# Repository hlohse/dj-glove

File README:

Windows
------------

Make sure the following software is installed:

    Visual Studio Express 2013
    Arduino IDE

To make use of virtual MIDI ports, use the following 3rd party software:

    Go to http://www.tobias-erichsen.de/
    Download and install loopMIDI
    Download the virtualMIDI SDK
    Copy the following virtualMIDI SDK C files to the ThirdParty directory:
        teVirtualMidi.h
        teVirtualMidi32.lib

Linux (Ubuntu 14.04)
-------------------------

Make sure the following packages are installed:

    g++ (>= 4.8)
    arduino
    libasound2-dev
    libbluetooth-dev

All Platforms
------------------

Pair your PC with the Arduino's Bluetooth module using the PIN 1234.

Adjust default Bluetooth address to your module's in PC/BluetoothDevice.cpp, BluetoothDevice::Arduino.

=========
  Misc
=========

Advanced project of Robotics Lab ST14, University of Heidelberg, Germany.
Authors: Jan-Lukas Tirpitz, Henning Lohse
Supervisors: Karsten Krispin, Thomas Kloepfer

Demo:
https://www.youtube.com/watch?v=biKKQlQEOuE

Project website (German): 
http://ornella.iwr.uni-heidelberg.de/ROBOTICSLAB/ROBPROJECTS/COMPLETED/2014SS_DJHANDSCHUH/index.html

Robotics Lab website:
http://joanna.iwr.uni-heidelberg.de/rlab/en/about

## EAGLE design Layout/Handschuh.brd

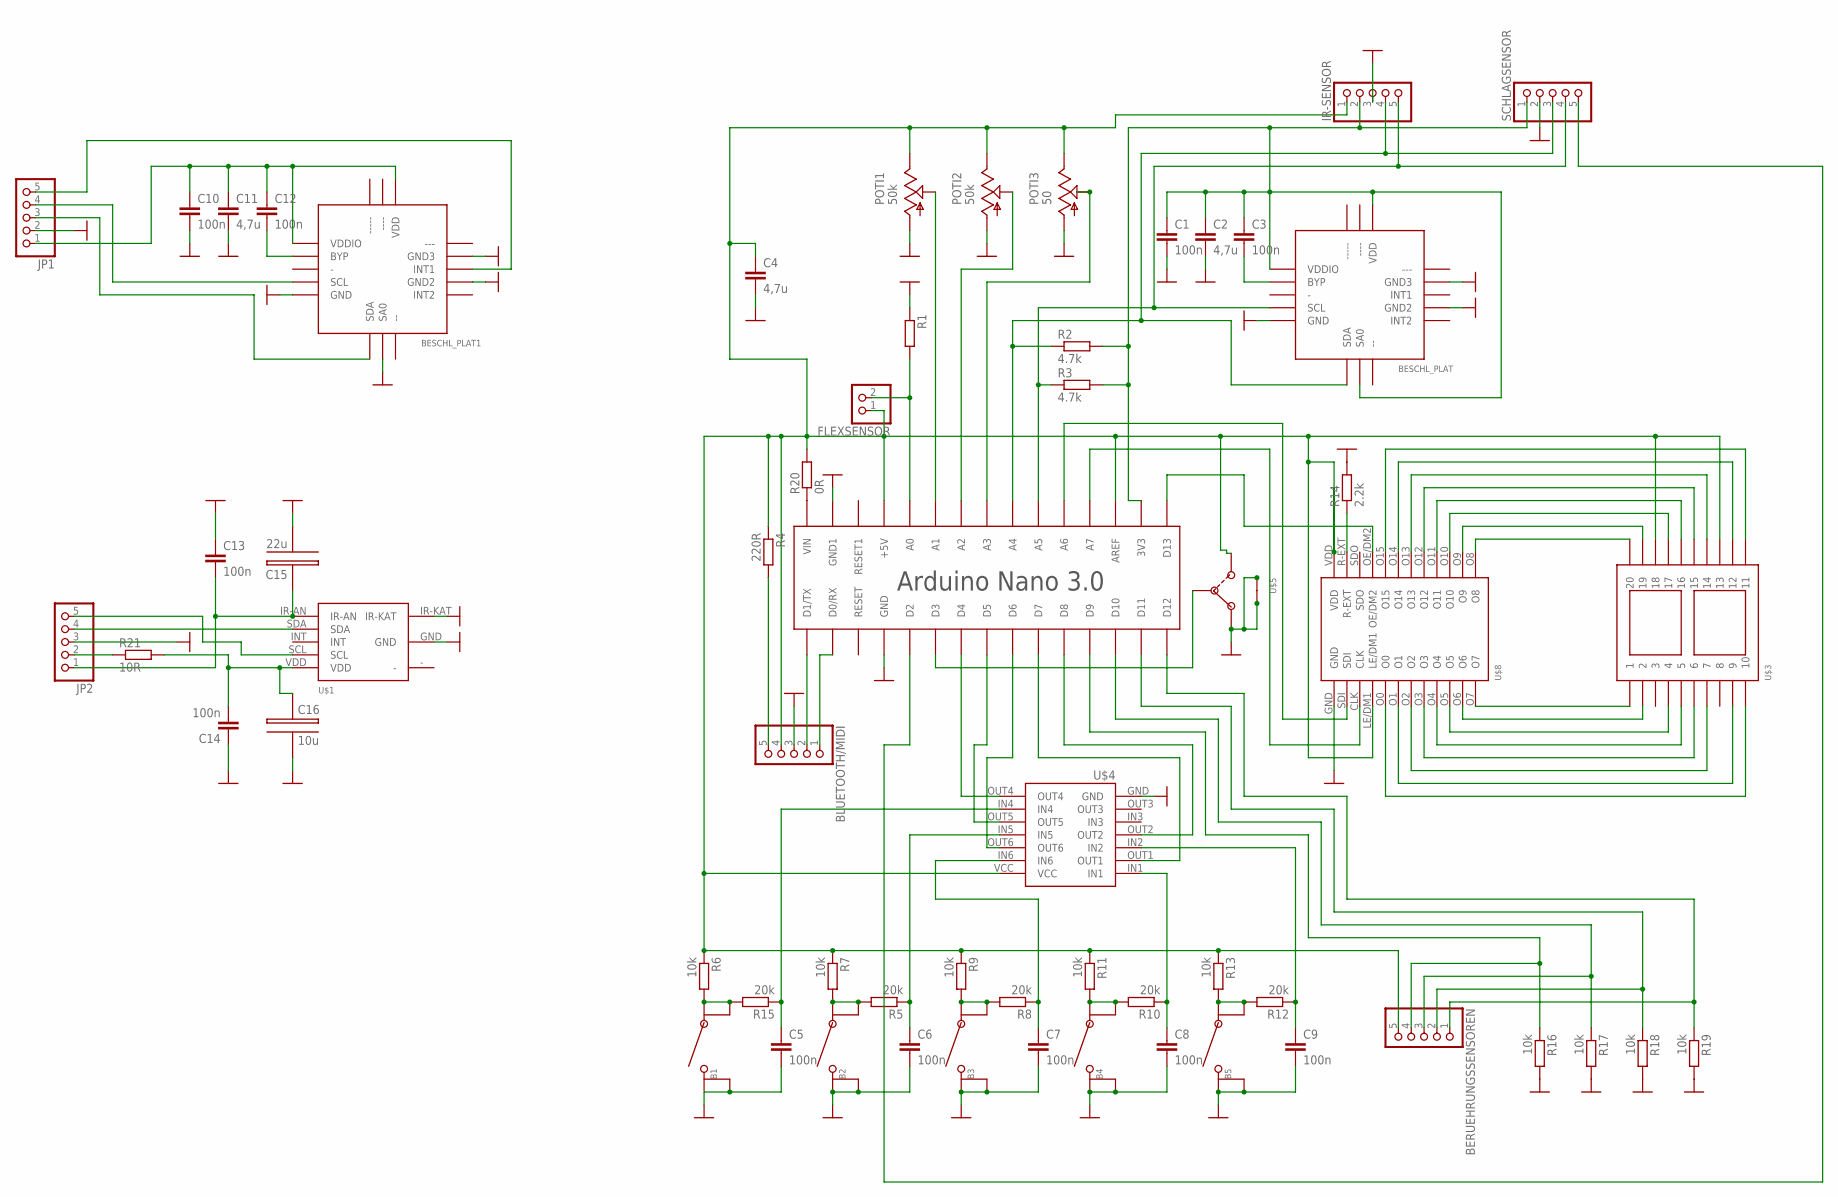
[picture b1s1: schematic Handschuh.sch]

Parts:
B1, B2, B3, B4, B5: BUTTON
BERUEHRUNGSSENSOREN: PINHD-1X5/90; 1X05/90
BESCHL_PLAT, BESCHL_PLAT1: BESCHLEUNIGSUNGSSENSOR; BESCHLEUNIGUNGSSENSOR
BLUETOOTH/MIDI: PINHD-1X5/90; 1X05/90
C1, C3, C5, C6, C7, C8, C9, C10, C12, C13, C14: 100n; C0805
C2, C4, C11: 4,7u; C0805
C15: 22u; 22U-KONDENSATOR
C16: 10u; 22U-KONDENSATOR
FLEXSENSOR: PINHD-1X2/90; 1X02/90
IR-SENSOR: PINHD-1X5/90; 1X05/90
JP1, JP2: PINHD-1X5/90; 1X05/90
POTI1, POTI2: 50k; POTI
POTI3: 50; POTI
R1: R-EU_M0805; M0805
R2, R3: 4.7k; M0805
R4: 220R; M0805
R5, R8, R10, R12, R15: 20k; M0805
R6, R7, R9, R11, R13, R16, R17, R18, R19: 10k; M0805
R14: 2.2k; M0805
R20: 0R; M0805
R21: 10R; M0805
SCHLAGSENSOR: PINHD-1X5/90; 1X05/90
U$1: IR-SENSOR
U$2: ARDUINONANO; PDIP-32
U$3: 7-SEGMENT
U$4: SCHMITT-TRIGGER
U$5: SCHALTER
U$8: 7-SEGMENT-TREIBER

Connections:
3,3V: BESCHL_PLAT.SA0, BESCHL_PLAT.VDD, BESCHL_PLAT.VDDIO, C1.1, C2.1, C3.1, IR-SENSOR.2, R2.2, R3.2, SCHLAGSENSOR.1, U$2.3V3
3,3V1: BESCHL_PLAT1.VDD, BESCHL_PLAT1.VDDIO, C10.1, C11.1, C12.1, JP1.1
5V: BERUEHRUNGSSENSOREN.5, BLUETOOTH/MIDI.4, C4.1, FLEXSENSOR.1, IR-SENSOR.1, POTI1.VCC, POTI2.VCC, POTI3.VCC, R4.1, R6.1, R7.1, R9.1, R11.1, R13.1, R20.2, U$2.+5V, U$2.AREF, U$3.13, U$3.18, U$4.VCC, U$5.3, U$8.LE/DM1, U$8.VDD
GND: B1.2, B2.2, B3.2, B4.2, B5.2, BESCHL_PLAT.GND, BESCHL_PLAT.GND2, BESCHL_PLAT.GND3, BESCHL_PLAT1.GND, BESCHL_PLAT1.GND2, BESCHL_PLAT1.GND3, BESCHL_PLAT1.SA0, BLUETOOTH/MIDI.3, C1.2, C2.2, C4.2, C5.2, C6.2, C7.2, C8.2, C9.2, C10.2, C11.2, C13.1, C14.1, C15.-, C16.-, IR-SENSOR.3, JP1.2, JP2.3, POTI1.GND, POTI2.GND, POTI3.GND, R1.1, R14.2, R16.2, R17.2, R18.2, R19.2, SCHLAGSENSOR.2, U$1.GND, U$1.IR-KAT, U$2.GND, U$2.GND1, U$4.GND, U$5.1, U$5.4, U$5.5, U$8.GND
unnamed: R20.1, U$2.VIN
unnamed: BESCHL_PLAT1.BYP, C12.2
unnamed: B1.3, B1.4, R6.2, R15.2
unnamed: FLEXSENSOR.2, R1.2, U$2.A0
unnamed: BESCHL_PLAT.BYP, C3.2
unnamed: SCHLAGSENSOR.5, U$2.D2
unnamed: POTI1.VALUE, U$2.A1
unnamed: POTI2.VALUE, U$2.A2
unnamed: POTI3.VALUE, U$2.A3
unnamed: BESCHL_PLAT1.SCL, JP1.4
unnamed: BLUETOOTH/MIDI.2, U$2.D1/TX
unnamed: BLUETOOTH/MIDI.1, U$2.D0/RX
unnamed: BLUETOOTH/MIDI.5, R4.2
unnamed: BESCHL_PLAT1.SDA, JP1.3
unnamed: C6.1, R5.1, U$4.IN5
unnamed: B2.3, B2.4, R5.2, R7.2
unnamed: C7.1, R8.1, U$4.IN6
unnamed: B3.3, B3.4, R8.2, R9.2
unnamed: C8.1, R10.1, U$4.IN1
unnamed: B4.3, B4.4, R10.2, R11.2
unnamed: C9.1, R12.1, U$4.IN2
unnamed: B5.3, B5.4, R12.2, R13.2
unnamed: U$2.D4, U$4.OUT4
unnamed: U$2.D5, U$4.OUT5
unnamed: U$2.D6, U$4.OUT6
unnamed: U$2.D7, U$4.OUT1
unnamed: U$2.D8, U$4.OUT2
unnamed: U$2.A6, U$8.SDI
unnamed: C5.1, R15.1, U$4.IN4
unnamed: U$2.A7, U$8.CLK
unnamed: U$3.9, U$8.O1
unnamed: U$3.1, U$8.O7
unnamed: U$3.2, U$8.O6
unnamed: U$3.4, U$8.O5
unnamed: U$3.5, U$8.O4
unnamed: U$3.6, U$8.O3
unnamed: U$3.7, U$8.O2
unnamed: U$3.10, U$8.O0
unnamed: U$3.20, U$8.O8
unnamed: U$3.19, U$8.O9
unnamed: U$3.17, U$8.O10
unnamed: U$3.16, U$8.O11
unnamed: U$3.15, U$8.O12
unnamed: U$3.14, U$8.O13
unnamed: U$3.12, U$8.O14
unnamed: U$3.11, U$8.O15
unnamed: BERUEHRUNGSSENSOREN.4, R16.1, U$2.D9
unnamed: R14.1, U$8.R-EXT
unnamed: U$2.D13, U$8.OE/DM2
unnamed: BESCHL_PLAT1.INT1, JP1.5
unnamed: BERUEHRUNGSSENSOREN.3, R17.1, U$2.D10
unnamed: BERUEHRUNGSSENSOREN.2, R18.1, U$2.D11
unnamed: BERUEHRUNGSSENSOREN.1, R19.1, U$2.D12
unnamed: U$2.D3, U$5.2
unnamed: BESCHL_PLAT.SCL, IR-SENSOR.5, R3.1, SCHLAGSENSOR.4, U$2.A5
unnamed: C13.2, C15.+, JP2.1, U$1.IR-AN
unnamed: C14.2, C16.+, R21.2, U$1.VDD
unnamed: BESCHL_PLAT.SDA, IR-SENSOR.4, R2.1, SCHLAGSENSOR.3, U$2.A4
unnamed: JP2.2, R21.1
unnamed: JP2.4, U$1.SDA
unnamed: JP2.5, U$1.SCL

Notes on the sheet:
Arduino Nano 3.0

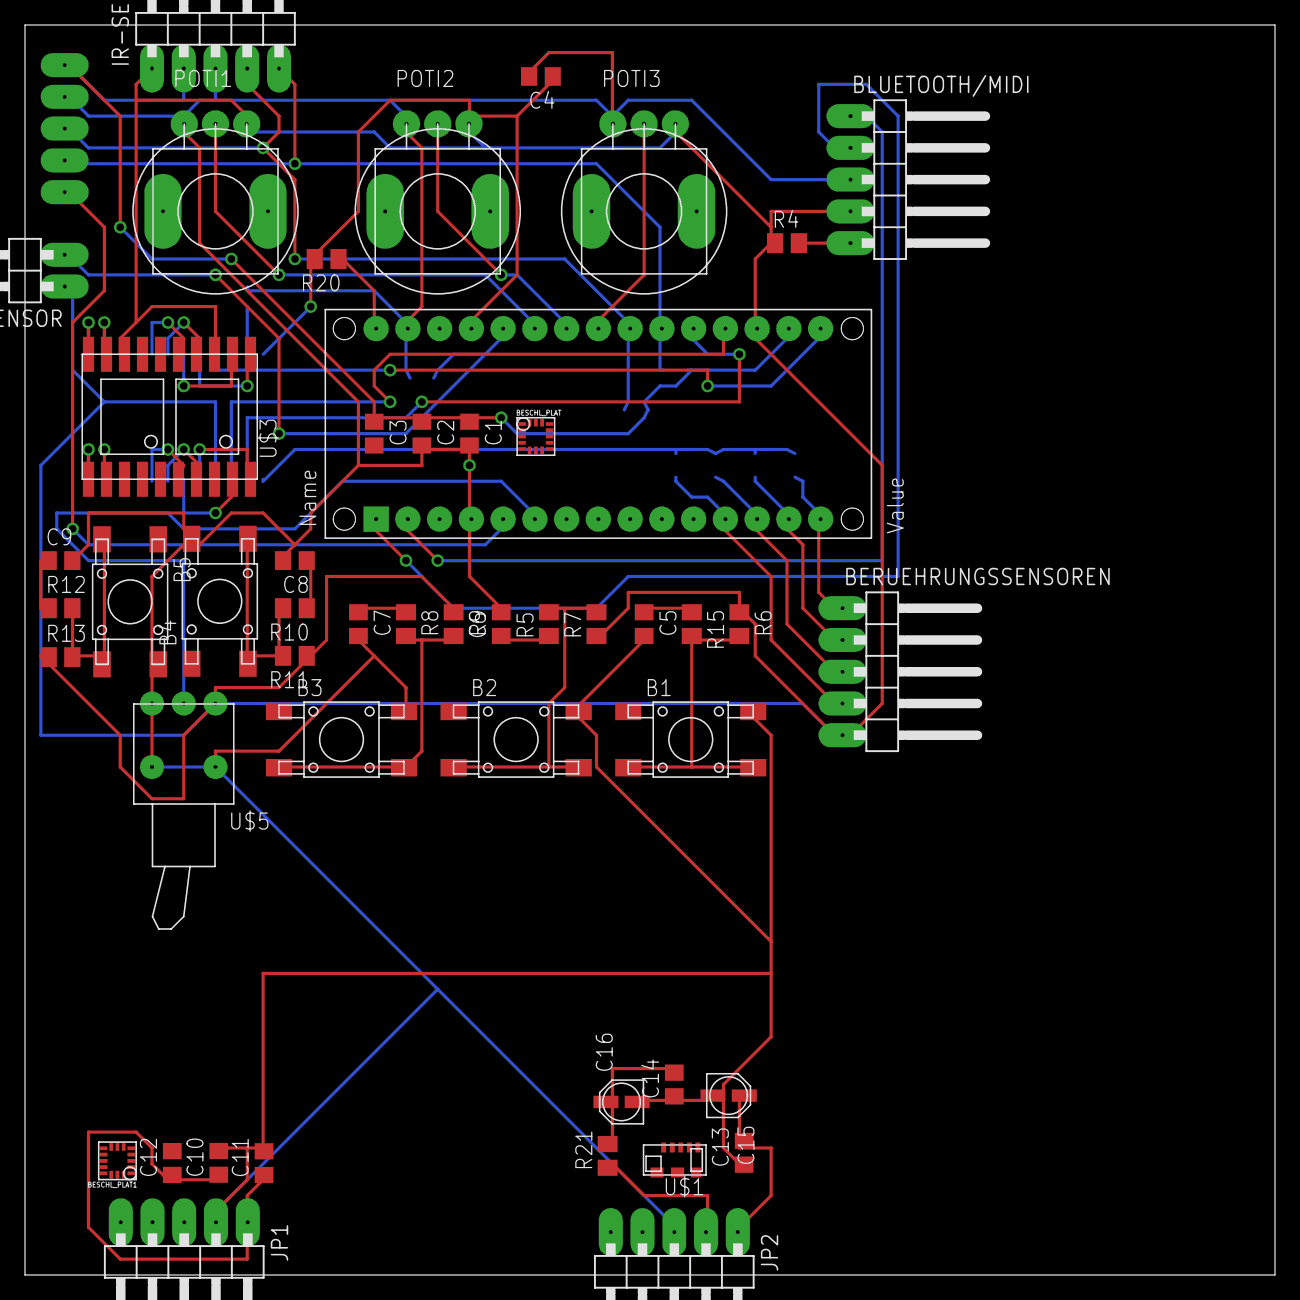
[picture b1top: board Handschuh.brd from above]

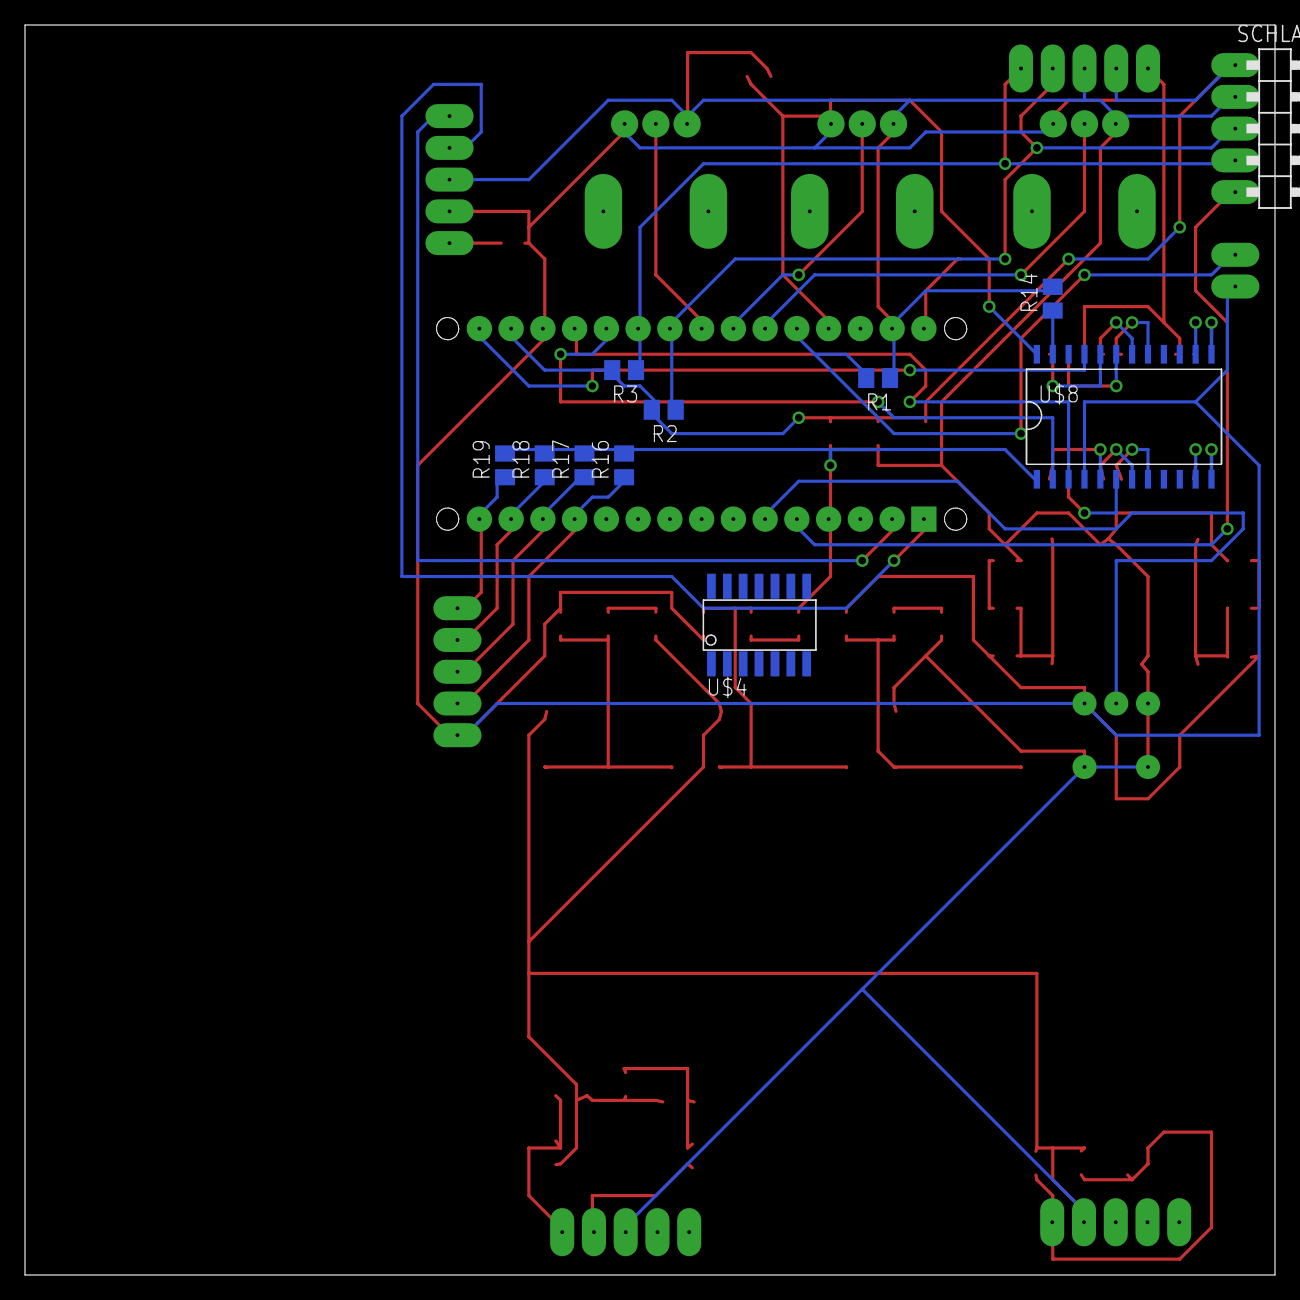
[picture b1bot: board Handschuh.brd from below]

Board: 2 copper layers, 100.0 x 100.0 mm, 60 parts (11 on the bottom side), 65 nets.

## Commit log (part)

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2014-06-17 * Added .gitignore * Ignores C++ and VisualStudio files (via GitHub)
2014-06-17 * Added build, lib, inc and src directories * build, inc and src have arduino and midiserver subdirs
2014-06-17 Revert "Added Arduino Blink basic example to sources"
    This reverts commit 96d4ca2e5d37cda4671e8fc9c7b83ebec26619f9.
2014-06-17 Revert "* Added build, lib, inc and src directories"
    This reverts commit 876984708795c58a9c3cb623dbc15fad2306fee0.
2014-06-18 Added upload.sh Bash script for easy binary upload
2014-06-19 Revert "Started Makefile including Arduino processing,"
    This reverts commit 1aae7c41ad6667d9326a8a3ee617025c9303064b.
2014-06-19 Revert "Added upload.sh Bash script for easy binary upload"
    This reverts commit 5ea77c0251e6820b0246ce1e51268587c1eec1c7.
2014-06-19 PC directory now has just common subdirectory. Projects will need their own directory
2014-06-19 Added Arduino.mk from https://github.com/sudar/Arduino-Makefile
2014-06-19 Added Bluetooth to Arduino common libs. It provides a SoftwareSerial and setup function for Bluetooth communication
2014-06-21 Compilable BtPingPong stub with Makefile
2014-06-21 * Added top-level Makefile * Executes Makefile for each project in Arduino directory * Can be configured via Config.mk
2014-06-21 Ignore .swo
2014-06-21 Implemented Arduino BtPingPong
2014-06-21 Implemented ISerial interface
2014-06-21 Added WaitUntilAvailable and GetLastError to ISerial
2014-06-21 * Renamed ISerial to Serial * Serial implements several methods using abstract methods * Removed code stubs from Bluetooth implemented by Serial
2014-06-21 Ignore *.run
2014-06-21 * Changed Serial to ISerial interface * Added ISerial::ReadNextAvailable * Changed Serial implementation to CommonSerial
2014-06-22 BluetoothDevice uses channel, constructs socket address correctly
2014-06-22 CommonSerial implements ISerial::GetLastError
2014-06-22 Implemented Bluetooth::Connect to connect to given device via Bluetooth RFCOMM socket
2014-06-22 Refactorings Bluetooth
2014-06-22 * Moved Platform.h to root directory * Added Bluetooth Channel and MAC
2014-06-22 ISerial's declared functions must take length parameter
2014-06-22 Fixed false implicit type casting of BluetoothDevice::channel_
2014-06-22 * Adopted ISerial changes to Bluetooth * As ioctl returns size of next message and not all socket data, WaitUntilAvailable uses read to buffer into buffer_ internally until the requested length is bu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
2014-06-22 * Fixed missing ISerial virtual destructor * Directory common in root directory to share infos between Arduino and PC projects * Move Platform.h to common * Created BtLatency.h in common to configure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
2014-06-26 Fixed make clean
2014-06-26 Added BluetoothCommands providing AT commands to configure Bluetooth module
2014-07-01 Heavily changed project structure: * Arduino projects are no longer compiled via Makefile * Use IDE to compile Arduino project from their ino file * Copy/link libraries into Arduino installation fold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
2014-07-01 Added Visual Studio 2013 solution
2014-07-01 Ported Bluetooth to Windows
2014-07-03 * Added Bluetooth::SetUp/::TearDown for Winsock init/cleanup * Link against Winsock2 library
2014-07-03 * BluetoothDevice uses channel as port on Windows * Bluetooth uses send/recv instead of _write/_read for Windows sockets
2014-07-03 * BtLatency project correctly links againt libdj-glove.dll/.lib * Needs keypress to terminate
2014-07-03 Implemented MidiSignal
2014-07-03 Implemented MidiPort for Windows using teVirtualMIDI
2014-07-05 * Midi declared byte/word types * enum instead of enum class as avr-gcc lacks the latter somehow * SplitPitchBend function
2014-07-05 Midi::CombinePitchBend
2014-07-05 * Moved bit fiddle code from MidiChannel to Midi * Comments for MidiChannel
2014-07-05 Added Missing class scope
2014-07-05 Implemented Entchen Arduino project. After receiving start signal '!', it sends MIDI signals playing Alle meine Entchen via Bluetooth :)
2014-07-05 * MidiChannel channel can be set later/changed * SignalLength returns number of Signal bytes
2014-07-05 Implemented MidiPlayer Arduino library. Provides a set of channels that can be played via Bluetooth. Sends number of signal bytes before 2-3 MIDI signal bytes
2014-07-05 MidiPlayer comments
2014-07-10 BtConfig Arduino project to change Bluetooth module's configurations
2014-07-10 * Fixed bit fiddles and casts in Midi * Adds offset to MIDI bytes for Bluetooth transmission, (MidiPlayer), removes them when receiving (MidiSignal) * Entchen is working
2014-07-10 Arduino BtLatency can switch between software and hardware serial via define falg
2014-08-04 Revert "Tracking missing files"
    Unnecessary .cxx files removed
    This reverts commit 1f7d2e939c30203b7ddfd110348c7e869583369d.
2014-08-04 Initial Readme
2014-08-04 MidiPort utilizes ALSA raw MIDI via libasound to play MIDI signals
2014-08-04 Uses virtual as name for snd_rawmidi_open to supposedly create a virtual MIDI port
2014-08-05 Upadted README for Ubuntu 14.04
2014-08-05 * Copied Midi to PC * Ported to C++11
2014-08-05 Added stub for DjGloveSignal to differentiate between punch and other sensor signals sent by the Arduino to transform to MIDI signals
2014-08-05 Removed Entchen projects
2014-08-05 Adopted Arduino MidiChannel code to PC MidiSignal to allow easy control of raw MIDI signals
2014-08-05 Initial stub for DjGloveServer PC project
2014-08-05 * Removed ISerial, CommonSerial * Bluetooth provides same essential methods, but throws exceptions instead of boolean methods and error message member * Adjusted BtLatency accordingly
2014-08-05 Fixed BluetoothDevice::Arduino
2014-08-05 Adjusted Visual Studio solution
2014-08-06 Defined sensor data protocol
2014-08-06 Implemented SignalsSensor's conversion of sent Arduino bytes to button and sensor values
2014-08-06 PunchSignal procudes example high pitched MIDI signal
2014-08-06 Fixed SensorsSignal::SetChannelFrom
2014-08-06 Implemented DjGlove struct to handle sensor data etc.
2014-08-06 Removed DjGloveSignal
2014-08-06 DjGlove processes data with DataProtocl to update sensor information. Stub for MIDI signal generation included
2014-08-06 Fixed missing push_back of MIDI signal stub
2014-08-06 Declared DataProtocl and DjGlove as EXPORT
2014-08-06 Added DjGloveServer stub with Boost Program Options dependency
2014-08-06 Implemented initial DjGloveServer
2014-08-06 Updated libdj-glove for Windows
2014-08-06 Added post build remove temp files step
2014-08-06 Removed boost from Makefile
2014-09-06 DataProtocol is now object applying to DjGlove member
2014-09-06 Implemented DjGloveServerArguments
2014-09-06 Adjusted and finalized DjGloveServer application; no Boost
2014-09-14 Upadtes VS solution
2014-09-15 Led without memcpy, references static array
2014-09-15 Implemented PushButton class with fixed number of calls to isPushed to debounce read digital value
2014-09-15 Stub for Flex class
2014-09-15 Initial DjGlove struct to group all component classes
2014-09-15 Additional default constructor Bluetooth for baud
2014-09-15 Put different classes into different sketch tabs
2014-09-15 Data now works byte-wise via nextByte
2014-09-15 DjGlove contain multiple poti, pushs
2014-09-15 * Renamed Push to Button * DjGlove contains additional touch buttons * Data transforms all buttons, potis, flex, channel, program; distance, orientation and flip button still missing
2014-09-15 Test code to print data bytes via Serial
2014-09-15 Fixed LED display
2014-09-15 Started UltraSound implementation, needs read fix
2014-09-24 Debounces button for pushed and not pushed
2014-09-24 Added UltraSound sensor to Data transmission
2014-09-24 Wire.begin in DjGlove constructor
2014-09-24 Implemented Gyro; currently blocking I2C calls
2014-09-24 Added Gyro to Data transmission
2014-09-24 Fixed struct initialization on Windows
2014-09-25 * Removed Bluetooth Arduino library * Adjusted existing Arduino projects accordingly
2014-09-25 DjGloveServer prints DjGlove data state after each receiving
2014-09-25 Inverted Poti value range so that left = 0, right = 127
2014-09-25 Fixed Gyro axis register addresses
2014-09-25 unsigned char instead of char for received data
2014-09-25 Arduino Data increments byte to send by 1
2014-09-25 Test
2014-09-26 Button provides assignOnPress/-Release methods to specify handler routines for pressed/released buttons
2014-09-26 * DjGlove is singleton; access instance pointer via DjGlove::instance() * Assigned push buttons 0, 1 to increase channel, program
2014-09-26 Data uses DjGlove singleton instance
2014-09-26 Revert "Data uses DjGlove singleton instance"
    This reverts commit b71d2b2479e4ebcd8bb72c9f36af3fffdcdc0d8c.
2014-09-26 null Bluetooth address before adding MAC
2014-09-26 Fixed display of program and channel via LED
2014-09-26 Displays P and C on LED on startup for 1.5s
2014-09-26 Gyro and UltraSound Wire calls with while(Wire.available())
2014-09-26 Added sync to DjGlove Arduino
2014-09-26 More gitignore
2014-09-26 Implemented Acceleration and Hit for hit detection and intensity Data transmission
2014-09-26 DjGlove and Server interpret punch data byte as hit intensity
2014-09-26 Fixed BtLatency
2014-09-29 * Added scripts directory * Added latency.gpl to plot BtLatency output via gnuplot * Example images for min, max and mean results
2014-09-29 Renamed Data to Protocol
2014-09-29 Added char based methods to Bluetooth
2014-09-29 Minor code simplification
2014-09-30 Put sensor loop switch into Protocol::nextSensorReadout
2014-09-30 Implemented RingFifo as FIFO data structe overwriting oldest values in circular/ring fashion if insertion occurs while full
2014-09-30 Fixed RingFifo::operator[] when not full
2014-09-30 Fixed RingFifo::insert to set m_is_full correctly
2014-09-30 Fixed Flex::read if buffer is empty (division by 0)
2014-09-30 * RingFifo offers getOrdered (by age) and getDirectly (by buffer index) * Flex uses RingFifo::getDirectly
2014-10-01 Minor code improvements
2014-10-01 Renamed DataProtocol to Protocol similar to Arduino's
2014-10-01 PC classes use m_name instead of name_ for member variables
2014-10-05 Added Bluetooth::Clear() to clear buffered data
2014-10-05 BtLatency PC determines time simply by receiving into Bluetooth buffer now; no checks are done. Might improve measurement precision.
2014-10-06 So, jetzt funktioniert der letzte Commit richtig
2014-10-07 Flex buffers 33 values, 3 for each call to Protocol::nextByte
2014-10-07 * Scaled Flex readout to 0..127 for closed hand to stretched hand * Faster Gyro readout using auto increment for axis registers
2014-10-07 * Only read Gyro's x and y axis * Protocol transfers x/y as 7 bit pairs (= 14 bit resolution per axis)
2014-10-07 Transfers Gyro signedness correctly
2014-10-07 Updated number of Procotol bytes
2014-10-07 Fixed Protocol bit shifts; fills 0 for <<, 1 for >>
2014-10-07 Fixed to hit detection, misplaced ifdef and sync
2014-10-07 Fixed y acceleration high byte
2014-10-07 Implemented Orientation to handle x/y axis acceleration with updating value from low/high byte via integration
2014-10-07 Orientation in integer degree +/- 0..360
2014-10-07 Probably fixed SOCKADDR_BTH definition
2014-10-07 Fixed SOCKADDR_BTH
2014-10-08 Fixed non-detection of hits with intensity 0
2014-10-08 tests
2014-10-08 Changed Gyro readout
2014-10-08 Erste Programm-Gehversuche
2014-10-08 ControllerPush-Klasse hinzugefügt. Sendet highValue beim Drücken und lowValue beim loslassen
2014-10-09 ControllerRange implements Controller
2014-10-09 * More explicit MidiSignal constructors for 1 or 2 values * Improved DjGlove readability using Register, brace-enclosed initializer lists for MidiSignal
2014-10-09 Use partitioned ControllerRange for theremin distance
2014-10-09 Serverprogramm 3: "ClipControl" und Verbesserungen von SP1 + 2 (SP=Serverprogramm)
2014-10-09 Plot for 1b latencies over delays
2014-10-09 plots for 1000 iterations 1 byte, n delay measurements
2014-10-09 Integrated ControllerGyro into DjGlove for effect control
2014-10-09 Andere Channel- und Programm-Anzahl, ControllerGyro-Korrektur und weitere Switch-Buttons
2014-10-09 Ein Controller-Nummer-Wechsel
2014-10-10 BtLatency measures roundtrip latency
2014-11-21 200 warmups, 1000 iterations for BtLatency
2014-11-21 Ignore compiled binaries
2014-11-21 Project information in README
2014-11-21 Added Akkubox 3D print files
2014-11-21 Replaced tabs with spaces
2014-11-27 README markdown + copyright
2014-11-27 Markup fixes...
